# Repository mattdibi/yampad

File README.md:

<h3 align="center">The Yampad project repository</h3>

<div align="center">

</div>

---

The Yampad project is an open-source, [QMK (Quantum Mechanical Keyboard Firmware)](https://github.com/qmk/qmk_firmware) powered, hot-swappable, RGB-backlighted, OLED featured, mechanical numpad. This repository will be used to share information about the project and instruction on how to use and assemble the Yampad.

**Designer's bio**: [Mattia Dal Ben (aka u/TiaMaT102)](mailto:matthewdibi@gmail.com) obtained a master's degree in Electrical Engineering with a specialization in Computer Science at the University of Udine. Currently works as a Software Engineer in R&D department for a big IoT and Embedded Computers company.

## Table of contents

- [Rationale](#rationale)
- [Default Layout](#default-layout)
- [Bill of materials](#bill-of-materials)
- [Assembly guide](#assembly-guide)
- [Firmware](#firmware)

## Rationale

The Yampad is a Macropad/Numpad which uses Cherry MX style mechanical switches laid out in the usual numeric pad layout. The only difference comes from the bottom row, which uses a 4 keys configuration, thus enabling the use of the macropad as a nav cluster.

The name comes from the acronym: **Y**et **A**nother **M**echanical num**PAD**, referring to the disruptive and innovative nature of the project.

The main goal of this project is to have a cheap, easy-to-build, feature-rich numpad which is completely open source.

Features:

- Cheap to build: the PCB can be manufactured for less than 1\$ per piece.
- Easy to source components.
- Easy to build.
- Hot swappable keys using _Kailh PCB sockets_.
- Arduino Pro Micro powered.
- QMK compatible.
- RGB backlighting support (optional).
- OLED 0.91" screen (optional).
- Completely open-source.

#### Useful links

- [YamPAD on Hackaday.io](https://hackaday.io/project/163491-yampad-feature-packed-open-source-macropad)

## Default Layout

## Bill of materials

| Qty | Item                                  | Notes                                                                                          |
| --- | ------------------------------------- | ---------------------------------------------------------------------------------------------- |
| 1   | Arduino Pro Micro (ATmega32u4)        | a.k.a. SparkFun Pro Micro                                                                      |
| 18  | Cherry MX compatible swtiches         |                                                                                                |
| 18  | SOD-123 1N4148/1N4148W diodes         |                                                                                                |
| 18  | Kailh PCB sockets CPG151101S11        |                                                                                                |
| 9   | WS2812B RGB LEDs                      | Optional                                                                                       |
| 9   | SMD 0805 100nF capacitors             | Optional (only required if WS2812B are installed)                                              |
| 1   | I2C 0.91" 128\*32 OLED Display Module | The ones using SSD1306 driver IC over I2C                                                      |
| 1   | 6mm\*6mm button switch                |                                                                                                |
| 1   | YamPAD PCB                            | [Order from PCBWay](https://www.pcbway.com/project/shareproject/YamPAD_mechanical_numpad.html) |
| 5   | M3 screws                             |                                                                                                |

## Assembly guide

There's no wrong order for the YamPAD assembly with the exception of the Arduino/OLED/ResetButton. Here I will suggest an order because I found more comfortable to solder the components this way.

1. Start with soldering the **WS2812 LEDs**. Start by applying solder to a pad, then heat it up while adding the component, finally solder the remaining pads.
2. Now add the **0805 100nF caps**. Use the same technique as before.
3. Add the **1N4148 diodes**.
4. Add the **CPG151101S11 Kailh PCB sockets**.
5. Add the **reset 6mm button switch**.
6. Add some electrical tape just to be sure.
7. Add the **Arduino Pro Micro** bottom side up.
8. Add the **OLED screen**
9. Move to the firmware section and you should be set!

### Assembly details

#### Step 1: WS2812 assembly

<p align="left">The LEDs have a direction, this is indicated by a small cut out corner showing a triangle on the LED itself that must align with a corner indicated on the PCB as a visible corner angle. Top left on images below.</p>

#### Step 2: Capacitors assembly

#### Step 3: Diodes assembly

<p align="left">The diodes have a direction, the side indicated by the line on the diode must align to the closed side of the shape on the PCB. Left on the three images below.</p>

#### Step 4: Kailh PCB sockets assembly

#### Step 5: Reset switch

#### Step 6: Electrical tape

#### Step 7: Arduino assembly

## Firmware

The firmware is available through [QMK firmware repository](https://github.com/qmk/qmk_firmware/tree/master/keyboards/yampad). Make example for this keyboard (after setting up your build environment):

```sh
make yampad:default
```

Example of flashing this keyboard:

```sh
make yampad:default:flash
```

See the [build environment setup](https://docs.qmk.fm/#/getting_started_build_tools) and the [make instructions](https://docs.qmk.fm/#/getting_started_make_guide) for more information. Brand new to QMK? Start with our [Complete Newbs Guide](https://docs.qmk.fm/#/newbs).

#### Pre-built

I also added a pre-built .HEX file in the 'firmware/' folder [here](https://github.com/mattdibi/yampad/tree/master/firmware) to test the electronics.

#### Via Support

I also added a porting to via .HEX file in the 'firmware/via_support' folder [here](https://github.com/mattdibi/yampad/tree/master/firmware/via_support) to load use .json file in via apps.

#### Stacked Acrylic Case

Acrylic case image gallery [here](https://github.com/mattdibi/yampad/tree/master/img/acrylic_case/).

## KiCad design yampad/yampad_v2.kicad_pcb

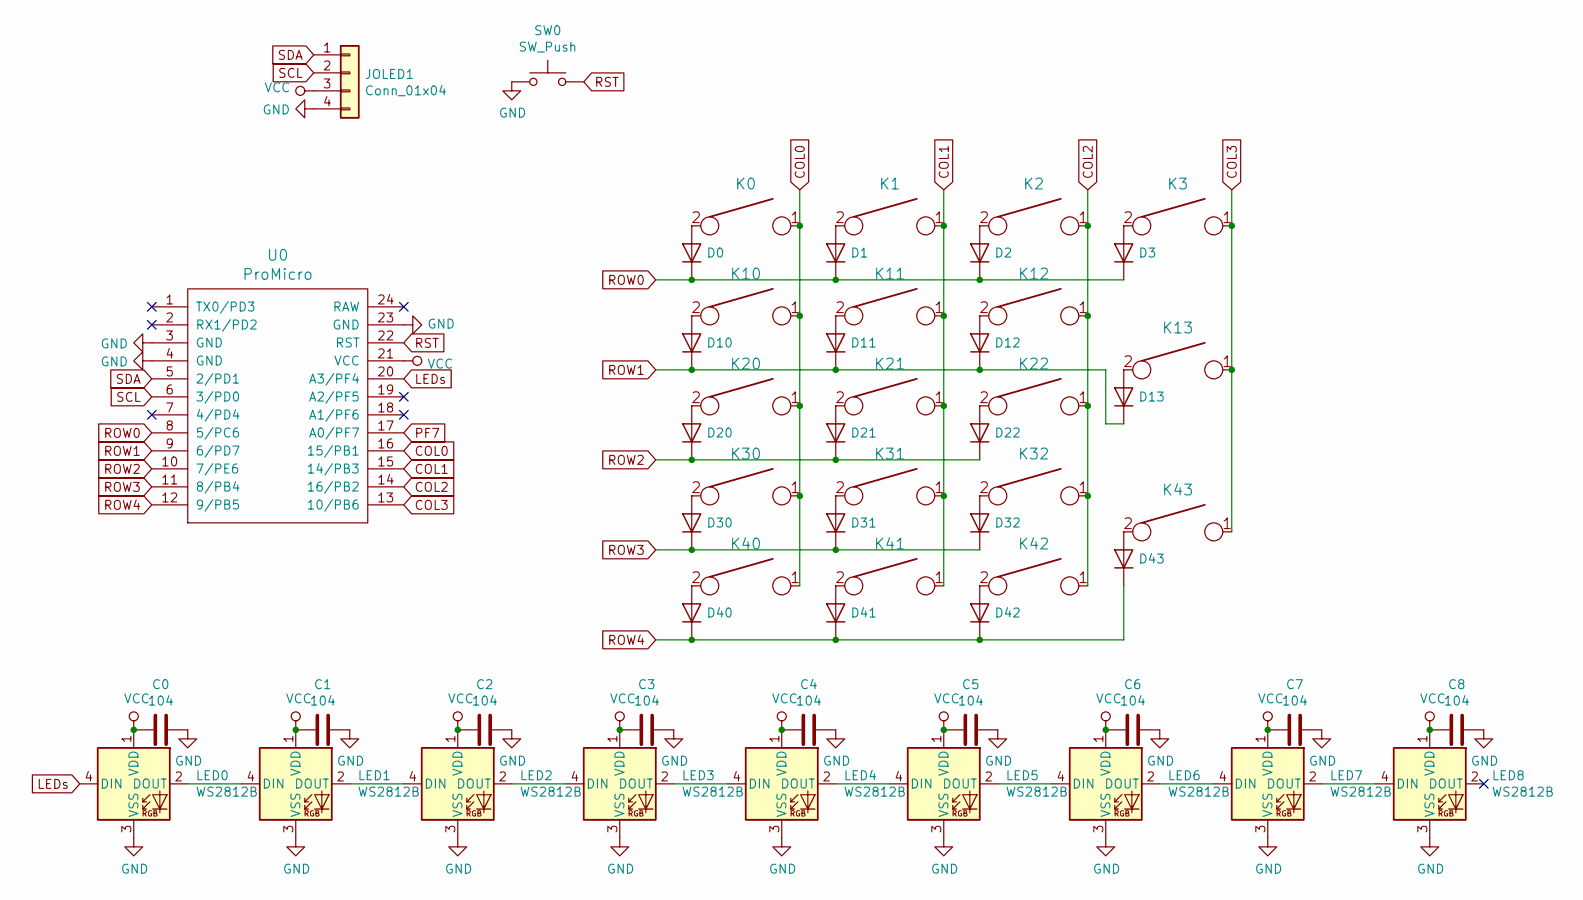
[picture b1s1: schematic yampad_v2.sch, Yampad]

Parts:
C0, C1, C2, C3, C4, C5, C6, C7, C8: 104; C_0805_2012Metric_Pad1.15x1.40mm_HandSolder
D0, D1, D2, D3, D10, D11, D12, D13, D20, D21, D22, D30, D31, D32, D40, D41, D42, D43: D; D_SOD123_axial-dual
JOLED1: Conn_01x04; PinHeader_1x04_P2.54mm_Horizontal
K0, K1, K2, K3, K10, K11, K12, K13, K20, K21, K22, K30, K31, K32, K40, K41, K42, K43: KEYSW; Kailh-PCB-Socket-1U-Cutout
LED0, LED1, LED2, LED3, LED4, LED5, LED6, LED7, LED8: WS2812B; LED_WS2812B_PLCC4_5.0x5.0mm_P3.2mm
SW0: SW_Push; SW_PUSH_6mm
U0: ProMicro; ArduinoProMicro

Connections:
COL0: K0.1, K10.1, K20.1, K30.1, K40.1, U0.16 (15/PB1)
COL1: K1.1, K11.1, K21.1, K31.1, K41.1, U0.15 (14/PB3)
COL2: K2.1, K12.1, K22.1, K32.1, K42.1, U0.14 (16/PB2)
COL3: K3.1, K13.1, K43.1, U0.13 (10/PB6)
GND: C0.1, C1.1, C2.1, C3.1, C4.1, C5.1, C6.1, C7.1, C8.1, JOLED1.4, LED0.3 (VSS), LED1.3 (VSS), LED2.3 (VSS), LED3.3 (VSS), LED4.3 (VSS), LED5.3 (VSS), LED6.3 (VSS), LED7.3 (VSS), LED8.3 (VSS), SW0.1, U0.3 (GND), U0.4 (GND), U0.23 (GND); also elsewhere on the board
LEDs: LED0.4 (DIN), U0.20 (A3/PF4)
unnamed: D0.2 (A), K0.2
unnamed: D1.2 (A), K1.2
unnamed: D2.2 (A), K2.2
unnamed: D3.2 (A), K3.2
unnamed: D10.2 (A), K10.2
unnamed: D11.2 (A), K11.2
unnamed: D12.2 (A), K12.2
unnamed: D13.2 (A), K13.2
unnamed: D20.2 (A), K20.2
unnamed: D21.2 (A), K21.2
unnamed: D22.2 (A), K22.2
unnamed: D30.2 (A), K30.2
unnamed: D31.2 (A), K31.2
unnamed: D32.2 (A), K32.2
unnamed: D40.2 (A), K40.2
unnamed: D41.2 (A), K41.2
unnamed: D42.2 (A), K42.2
unnamed: D43.2 (A), K43.2
unnamed: LED0.2 (DOUT), LED1.4 (DIN)
unnamed: LED1.2 (DOUT), LED2.4 (DIN)
unnamed: LED2.2 (DOUT), LED3.4 (DIN)
unnamed: LED3.2 (DOUT), LED4.4 (DIN)
unnamed: LED4.2 (DOUT), LED5.4 (DIN)
unnamed: LED5.2 (DOUT), LED6.4 (DIN)
unnamed: LED6.2 (DOUT), LED7.4 (DIN)
unnamed: LED7.2 (DOUT), LED8.4 (DIN)
PF7: U0.17 (A0/PF7)
ROW0: D0.1 (K), D1.1 (K), D2.1 (K), D3.1 (K), U0.8 (5/PC6)
ROW1: D10.1 (K), D11.1 (K), D12.1 (K), D13.1 (K), U0.9 (6/PD7)
ROW2: D20.1 (K), D21.1 (K), D22.1 (K), U0.10 (7/PE6)
ROW3: D30.1 (K), D31.1 (K), D32.1 (K), U0.11 (8/PB4)
ROW4: D40.1 (K), D41.1 (K), D42.1 (K), D43.1 (K), U0.12 (9/PB5)
RST: SW0.2, U0.22 (RST); also elsewhere on the board
SCL: JOLED1.2, U0.6 (3/PD0); also elsewhere on the board
SDA: JOLED1.1, U0.5 (2/PD1); also elsewhere on the board
VCC: C0.2, C1.2, C2.2, C3.2, C4.2, C5.2, C6.2, C7.2, C8.2, JOLED1.3, LED0.1 (VDD), LED1.1 (VDD), LED2.1 (VDD), LED3.1 (VDD), LED4.1 (VDD), LED5.1 (VDD), LED6.1 (VDD), LED7.1 (VDD), LED8.1 (VDD), U0.21 (VCC); also elsewhere on the board

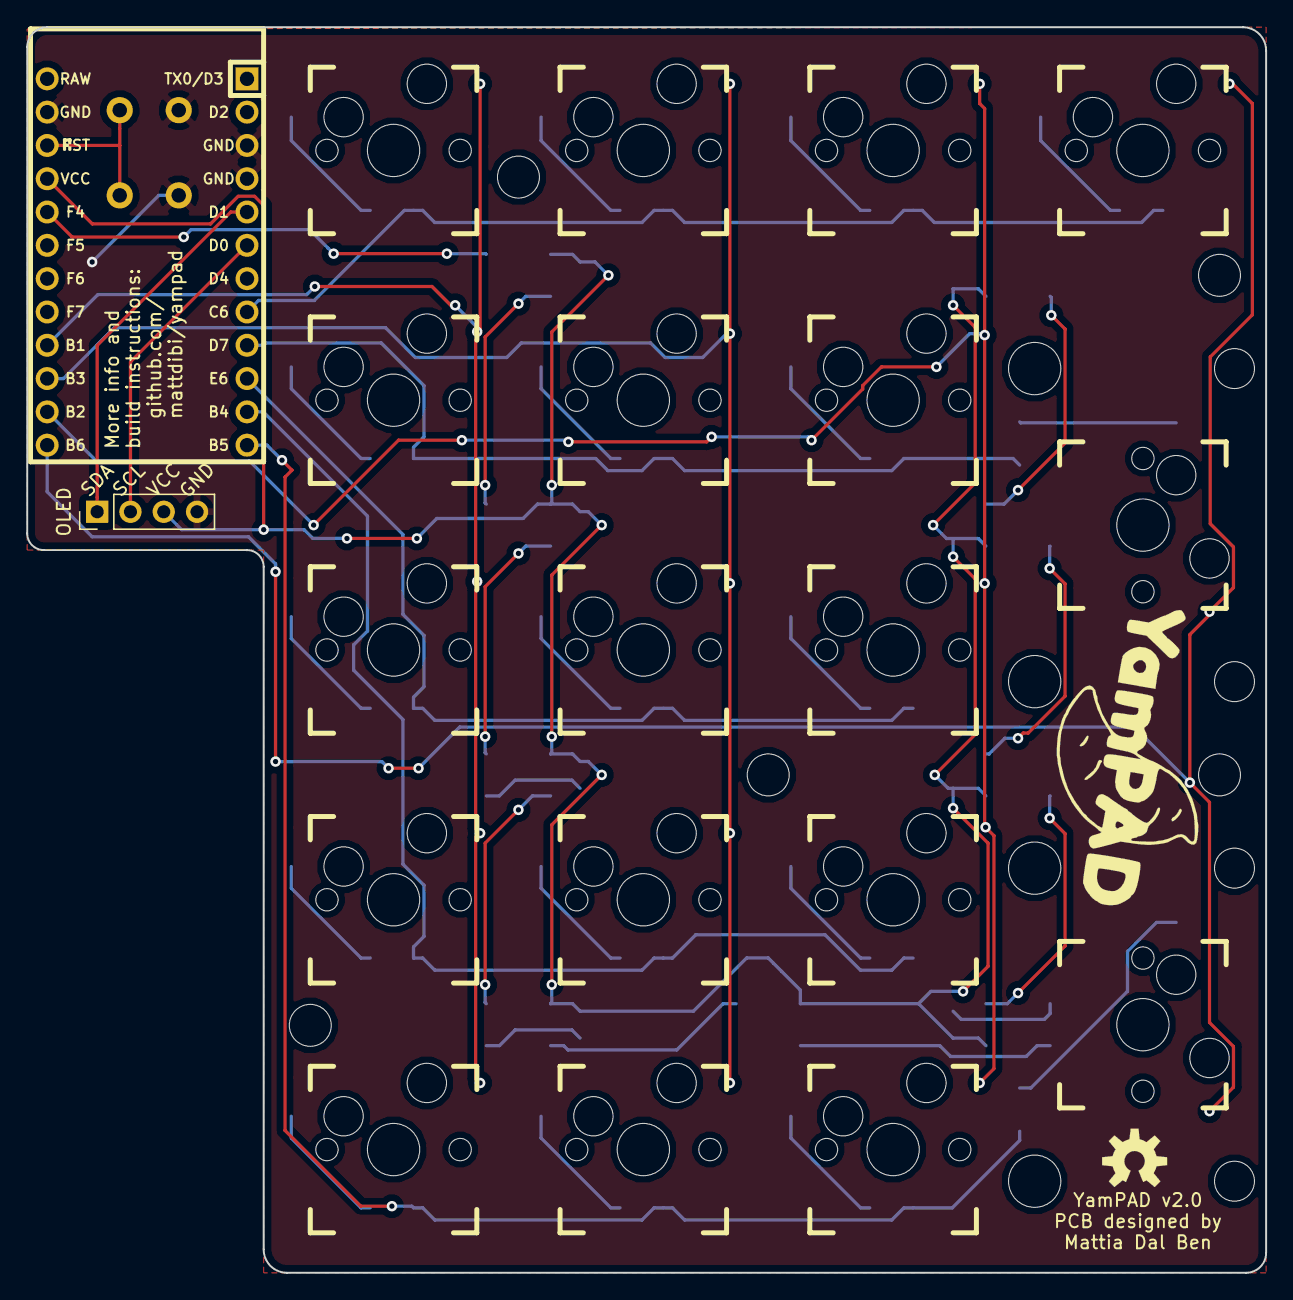
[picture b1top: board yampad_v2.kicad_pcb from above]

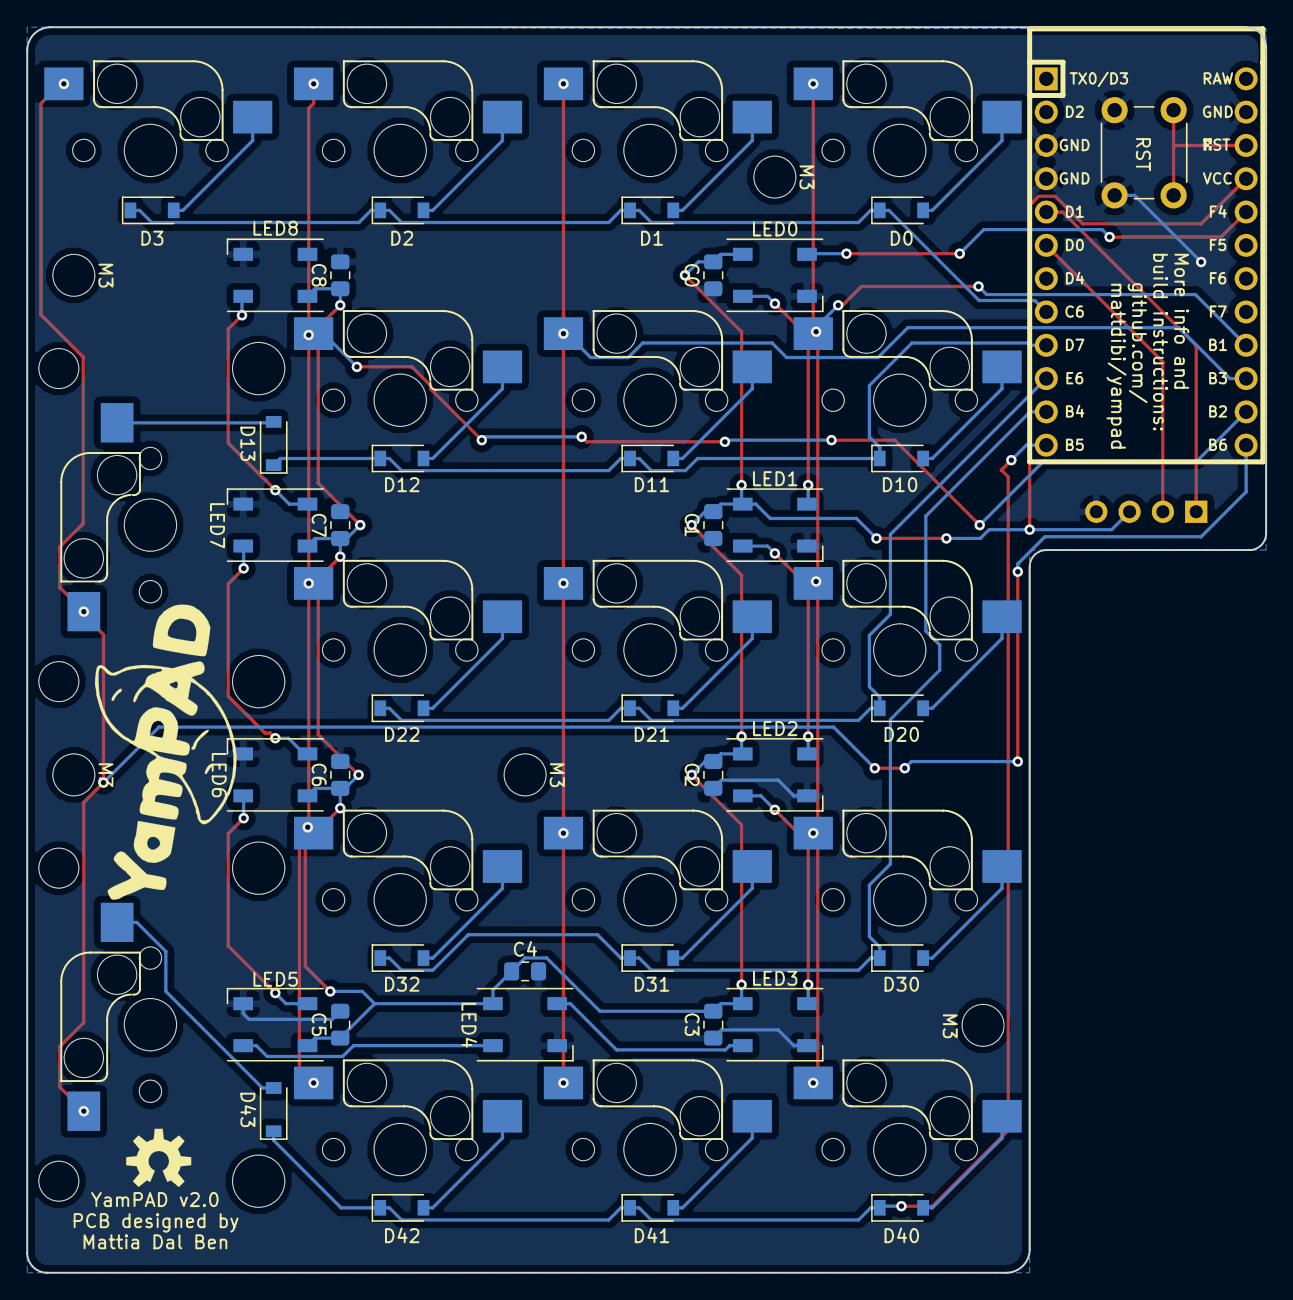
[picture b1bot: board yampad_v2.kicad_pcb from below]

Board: 2 copper layers, 94.5 x 95.0 mm, 62 parts (43 on the bottom side), 41 nets.

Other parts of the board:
M3, M3#2, M3#3, M3#4, M3#5: MountingHole_3.2mm_M3
OLED: Conn_01x04; PinHeader_1x04_P2.54mm_Vertical
RST: SW_Push; SW_PUSH_6mm

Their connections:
GND: OLED.4, RST.1; also elsewhere on the board
RST: RST.2; also elsewhere on the board
SCL: OLED.2; also elsewhere on the board
SDA: OLED.1; also elsewhere on the board
VCC: OLED.3; also elsewhere on the board

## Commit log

2019-04-30 Added README
2019-04-30 Added default layout section
2019-04-30 Added shameless donation button
2019-04-30 Corrected typo
2019-04-30 Added goal
2019-04-30 Scaled YamPAD logo
2019-05-06 Added PCB pic
2019-05-18 Added PCB files
2019-05-18 Added firmware link
2019-05-18 Added firmware instructions
2019-05-18 Changed main image
2019-05-19 Added Hackaday link
2019-05-20 Added BOM
2019-05-20 Added .dxf containing reference dimensions
2019-05-20 Added link for PCBWay ordering
2019-05-25 Added pre-built firmware file
2019-05-25 Added link to the folder
2019-05-25 Updated layout
2019-05-25 Improved images
2019-05-26 Added temporary fix for OLED screen not turning off
2019-06-02 Updated firmware with most recent version
2019-06-08 Added Fusion360 design file
2019-06-08 Added written instructions
2019-06-08 Added stage pics
2019-06-08 Added detailed instructions
2019-06-08 Resized images
2019-06-08 Added diodes installation details
2019-06-08 Removed stages
2019-06-08 Added "Rationale" pic
2019-06-08 Assembly instructions (#1)
    * Added written instructions
    * Added stage pics
    * Added detailed instructions
    * Resized images
    * Added diodes installation details
    * Removed stages
2019-09-01 Updated default layout
2019-09-01 Added wood and aluminium case files
2019-09-15 Clarified needed microcontroller in BOM
    See https://github.com/mattdibi/yampad/issues/2
2020-05-30 Improved README looks
2020-05-30 Added Table of contents
2020-05-30 Added KiCAD sources
2020-05-30 Added KiCAD sources (#4)
2020-10-03 Added details for LED and diode orientation (#10)
    * Update README.md
    * Update README.md
2020-10-12 new acrylic case design, firmware make files, new traditional layout
2020-10-12 minor tweaks to settings to be compatible with PR with qmkfirmware
2021-01-23 Added yampad_v3-Fusion360.step file
2021-01-23 Added yampad_v2-Fusion360.step file
2021-01-23 Fixed missing plate in yampad_v3-Fusion360.step
2021-07-04 DOCS: Updated firmware section
2021-07-04 DOCS: Updated firmware section (#15)
2021-11-09 add porting via
2021-11-09 add Acrylic Case
2021-11-09 fix location
2021-11-09 location
2021-11-09 location fix
2021-11-09 add readme case and via information
2021-11-13 change format case
2021-11-14 Add Via porting and Stacked Acrylic Case (#16)
    * add porting via
    * add Acrylic Case
    * fix location
    * location
    * location fix
    * add readme case and via information
2021-11-14 Fixed formatting issue on README
2024-12-14 docs: add note about WS2812B
2024-12-14 docs: add note about WS2812B (#25)
2026-05-26 Remove broken link from README

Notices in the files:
README.md:
License: MIT
